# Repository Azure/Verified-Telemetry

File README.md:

# PROJECT ARCHIVED

This repository has been archived and is now read-only. It will continue to be available for viewing purposes, however caution should be used as security fixes are no longer being applied.

---

# Verified Telemetry for Azure IoT

## Overview

The quality of sensor data is fundamental for driving IoT adoption. Since IoT sensors are often made of low-cost components, deployed in-the-wild and in harsh environments, they are prone to failures leading to faulty or dirty data. The effect of this faulty data will lead to the well-known garbage-in / garbage-out process, leading to cascading ill-effects upstream and at times catastrophic decisions.  

Verified Telemetry (VT) is a state-of-the-art solution to determine the health of the sensor, i.e., working or faulty, which is consequently used to determine the quality of the sensed data. This is achieved by devising an intelligent “sensor fingerprint”, a set of unique electrical characteristics that differs between working and faulty sensors. The fingerprints can detect faults for a wide variety of off-the-shelf sensors and can be easily implemented with lightweight software code running on the IoT device. This novel approach empowers customers with a reliable and automated way to remotely measure and observe the health of the sensor in real-time alongside the data collected. The data associated with a validated fingerprint results in Verified Telemetry.

Verified Telemetry uses two technologies - FallCurve for analog sensors, CurrentSense for Digital Sensors. 

### Fall Curve

It reads the 

## API documentation

Refer to the [Verified Telemetry API](https://azure.github.io/Verified-Telemetry) for details on the VT Azure RTOS and FreeRTOS SDKs and how they are used.

## Resource Requirements

Verified Telemetry is designed to run on resource contrained MCUs, flash and RAM is limited. Below is our resource requirements for Verified Telemetry for a size optimized (-Os) binary:

| Type      | Size  |
| --------- | ----- |
| **Flash** | 13.0 kB |
| **RAM**   | 4.6 kB |

## Plug and Play

Verified Telemetry Library provides capabilities for interaction using a Plug and Play Model.
Details about this model can be found [here](./PnPModel).

## Samples

We provide multiple device and solution samples to showcase the usage of Verified Telemetry. Please follow the samples below to see Verified Telemetry in action.

To get you started with the device, refer to the following device samples for Azure RTOS and FreeRTOS:
* [Azure RTOS samples](https://github.com/Azure/Verified-Telemetry-Device-Sample)
* [FreeRTOS samples](https://github.com/Azure-Samples/Verified-Telemetry-FreeRTOS-Sample)

To get you started with the solution, refer to the following Grafana sample:
* [Grafana solution sample](https://github.com/Azure/Verified-Telemetry-Solution-Sample) showcases how Verified Telemetry can be utilized in real world scenarios.

## Using Verified Telemetry

Verified Telemetry utilizes CMake for building the project. To integrate Verified Telemetry into your projects build system follow these steps:

1. Using Git, submodule VT into your project:

    ```shell
    git submodule add https://github.com/Azure/Verified-Telemetry.git
    ```
1. In your CMake, set `VT_MIDDLEWARE_RTOS` to either `AZURE_RTOS` or `FREERTOS` depending on which middleware is appropriate for your project:

    ```cmake
    set(VT_MIDDLEWARE_RTOS "AZURE_RTOS")
    ```
1. In your CMake, add the VT directory:

    ```cmake
    add_subdirectory(verified-telemetry)
    ```
1. In your CMake, add VT into your targets link library:

    ```cmake
    target_link_libraries(${PROJECT_NAME}
        az::iot::vt
    )
    ```

## Porting to your Platform

Verified Telemetry requires platform specific functions to be defined at the application layer and then passed to VT during initialization.

> **NOTE**
> * Refer to [vt_device_driver.h](./inc/platform/vt_device_driver.h) for function declarations
> * Refer to [vt_device_driver_template.c](./templates/vt_device_driver_template.c) for a template for implementation of the platform functions.
> * Samples for implementation of platform functions can also be found in the [Device samples](https://github.com/Azure/Verified-Telemetry-Device-Sample/blob/main/MXChip/AZ3166/app/sample_vt_device_driver.c).

The application developer will implement the following functions:

 | Function  | Implementation Requirements  | FallCurve Required? |
 | --------- | ---------------------------- | ------------------- |
 | adc_single_init   | Initialize ADC when the controller and channel are passed as arguments         | REQUIRED |
 | adc_single_read   | Return ADC data when the controller and channel are passed as arguments        | REQUIRED |
 | adc_buffer_read   | Return buffer filled with ADC data using DMA/non-blocking read when the controller, channel, sampling frequency and sample length are passed as arguments | REQUIRED |
 | gpio_on           | Set a GPIO pin HIGH when the GPIO port and pin are passed as arguments         | REQUIRED |
 | gpio_off          | Set a GPIO pin LOW when the GPIO port and pin are passed as arguments          | REQUIRED |
 | tick_init         | Initialize a tick counter with a time resolution that is passed as an argument | REQUIRED |
 | tick_deinit       | De-initialize a running tick counter                                           | REQUIRED |
 | tick              | Return the present tick value                                                  | REQUIRED |
 | interrupt_enable  | Enable global interrupts on the MCU                                            | OPTIONAL |
 | interrupt_disable | Disable global interrupts on the MCU                                           | OPTIONAL |

## Support

If you need support, please see our [SUPPORT.md](./SUPPORT.md) file.

## Contributing

For details on contributing to this repository, see the [contributing](CONTRIBUTING.md) guide.

## Reporting Security Vulnerabilities

If you believe you have found a security vulnerability in any Microsoft-owned repository that meets Microsoft's definition of a security vulnerability, please report it to the [Microsoft Security Response Center](SECURITY.md).

## License

Verified Telemetry are licensed under the [MIT](LICENSE.txt) license.

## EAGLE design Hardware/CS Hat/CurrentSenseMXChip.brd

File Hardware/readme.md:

# PCB files for Verified Telemetry Hardware 

Includes Gerber, Assembly, Schematic, Board and BOM files for manufacturing of hardware required to setup Verified Telemetry on MX Chip, STM32 and ESP32. 
The hardware consists of CS hat and CS baseboards specific to MCU.

CS hat contains the components required to sample signals and communicate them to the MCU using SPI. CS hat gets fixed on the baseboard and no other wiring is required to setup the hardware. 

Baseboards are used to route the right pins on the MCU to the CS hat for VT functioning. 

## ST Microelectronics B-L475E-IOT01A / B-L4S5I-IOTOA1 Discovery kit Baseboard

## MXChip AZ3166 IoT DevKit Baseboard

## ESP 32 Baseboard

## CurrentSense (CS) Hat

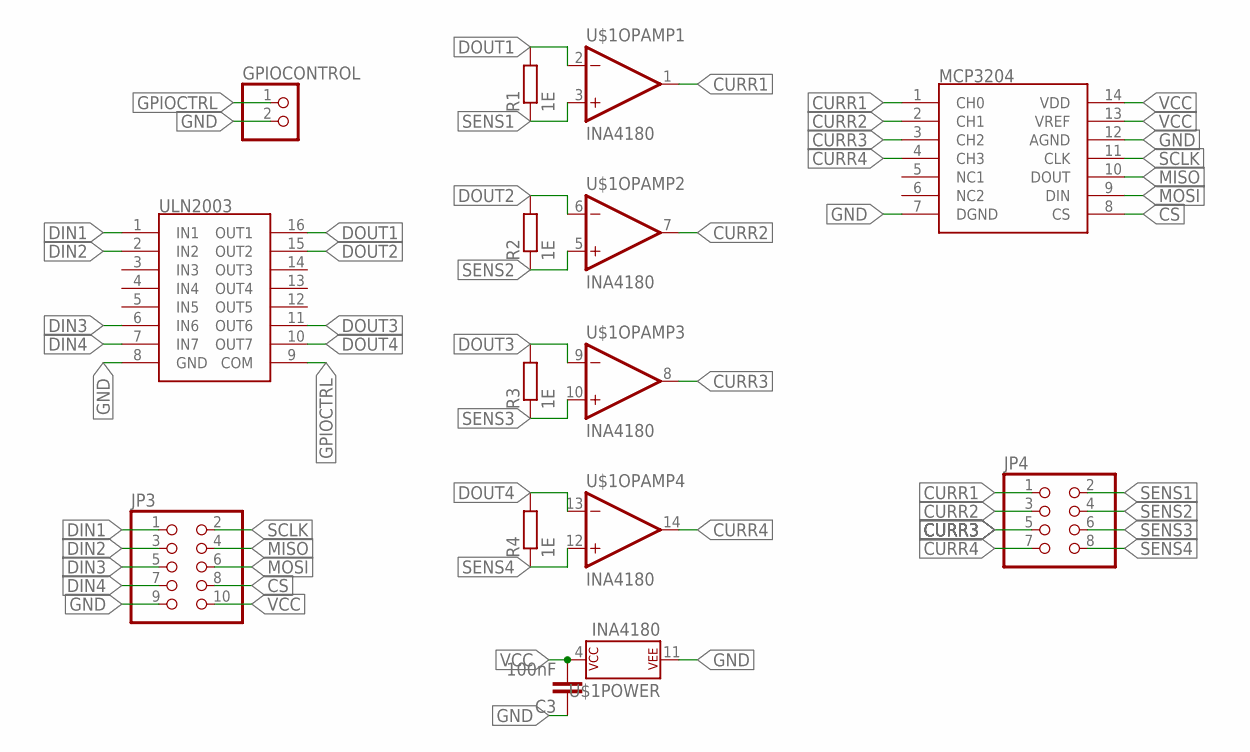
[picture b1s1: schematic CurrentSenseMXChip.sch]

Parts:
C3: 100nF; C1206
GPIOCONTROL: PINHD-1X2; 1X02
JP3: PINHD-2X5; 2X05
JP4: PINHD-2X4; 2X04
R1, R2, R3, R4: 1E; R1206
U$1: INA4180; TSSOP-14
U$2: ULN2003; SO16
U$3: MCP3204; TSSOP-14

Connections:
CS: JP3.8, U$3.8 (CS)
CURR1: JP4.1, U$1.1 (OUT), U$3.1 (CH0)
CURR2: JP4.3, U$1.7 (OUT), U$3.2 (CH1)
CURR3: JP4.5, U$1.8 (OUT), U$3.3 (CH2)
CURR4: JP4.7, U$1.14 (OUT), U$3.4 (CH3)
DIN1: JP3.1, U$2.1 (IN1)
DIN2: JP3.3, U$2.2 (IN2)
DIN3: JP3.5, U$2.6 (IN6)
DIN4: JP3.7, U$2.7 (IN7)
DOUT1: R1.2, U$1.2 (-IN), U$2.16 (OUT1)
DOUT2: R2.2, U$1.6 (-IN), U$2.15 (OUT2)
DOUT3: R3.2, U$1.9 (-IN), U$2.11 (OUT6)
DOUT4: R4.2, U$1.13 (-IN), U$2.10 (OUT7)
GND: C3.1, GPIOCONTROL.2, JP3.9, U$1.11 (P$V-), U$2.8 (GND), U$3.7 (DGND), U$3.12 (AGND)
GPIOCTRL: GPIOCONTROL.1, U$2.9 (COM)
MISO: JP3.4, U$3.10 (DOUT)
MOSI: JP3.6, U$3.9 (DIN)
SCLK: JP3.2, U$3.11 (CLK)
SENS1: JP4.2, R1.1, U$1.3 (+IN)
SENS2: JP4.4, R2.1, U$1.5 (+IN)
SENS3: JP4.6, R3.1, U$1.10 (+IN)
SENS4: JP4.8, R4.1, U$1.12 (+IN)
VCC: C3.2, JP3.10, U$1.4 (P$V+), U$3.13 (VREF), U$3.14 (VDD)

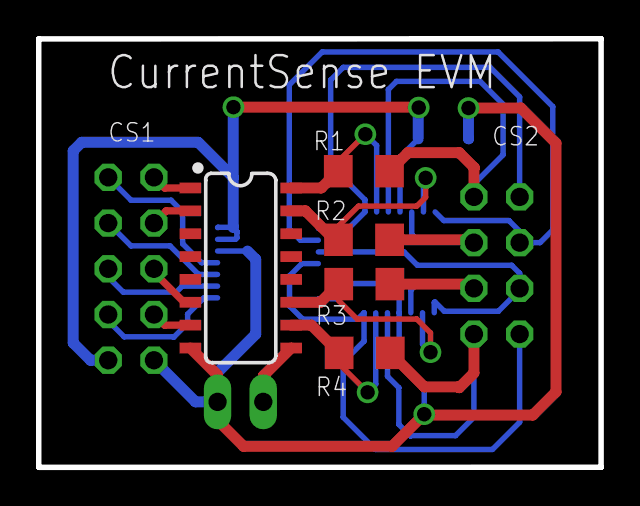
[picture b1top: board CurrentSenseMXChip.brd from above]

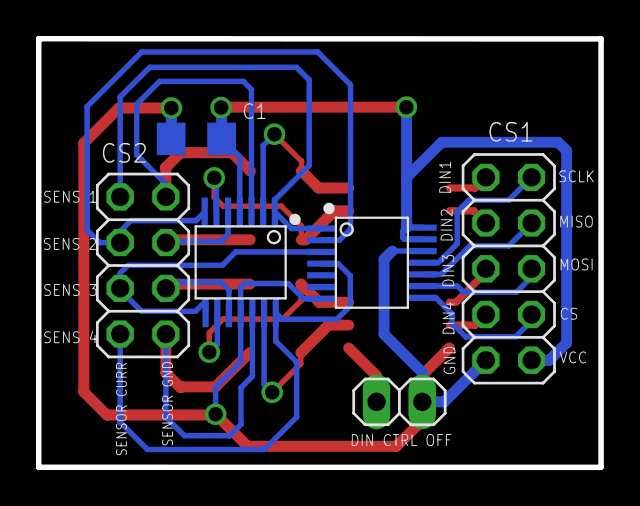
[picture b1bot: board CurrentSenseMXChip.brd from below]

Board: 2 copper layers, 31.2 x 23.8 mm, 11 parts (6 on the bottom side), 23 nets.

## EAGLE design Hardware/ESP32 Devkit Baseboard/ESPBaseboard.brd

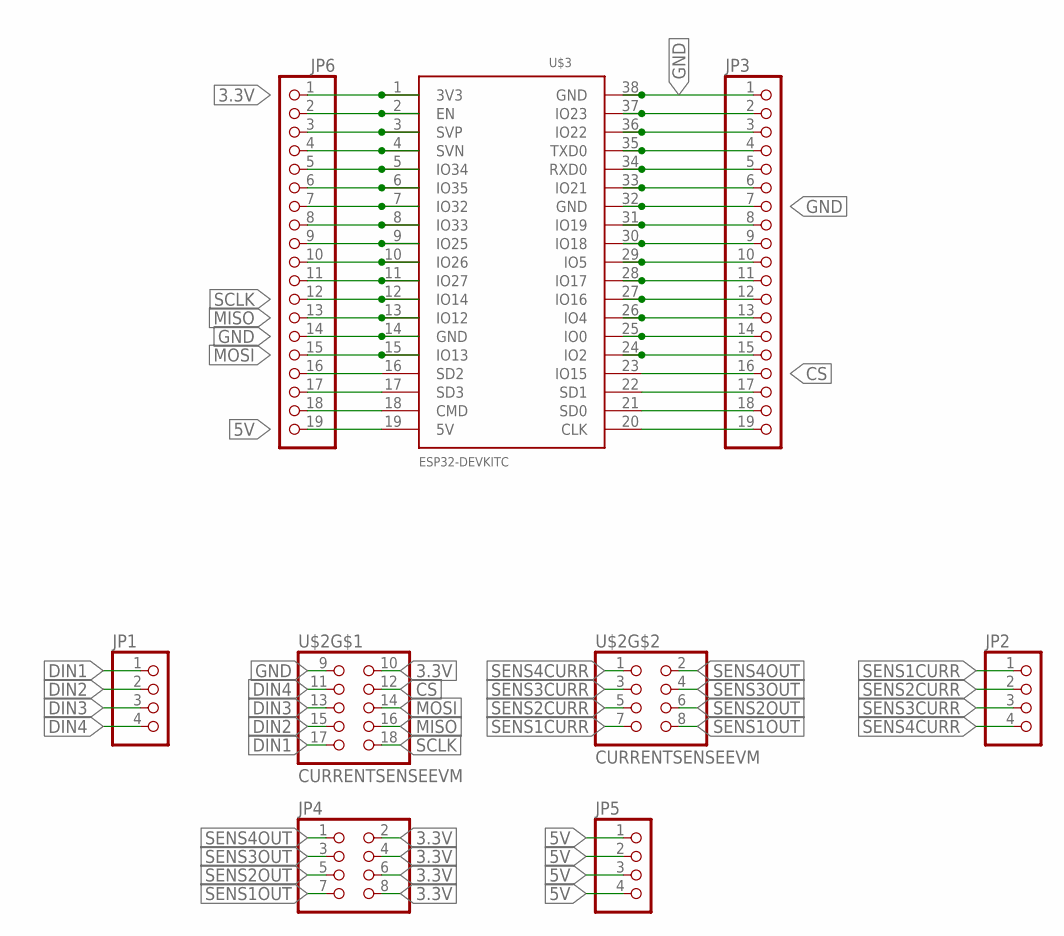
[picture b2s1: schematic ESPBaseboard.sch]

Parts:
JP1, JP2, JP5: PINHD-1X4; 1X04
JP3, JP6: PINHD-1X19; 1X19
JP4: PINHD-2X4; 2X04
U$2: CURRENTSENSEEVM
U$3: ESP32DEVKITC; ESP32-DEVKITC

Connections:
3.3V: JP4.2, JP4.4, JP4.6, JP4.8, JP6.1, U$2.10 (2), U$3.1 (3V3)
5V: JP5.1, JP5.2, JP5.3, JP5.4, JP6.19, U$3.19 (5V)
CS: JP3.10, JP3.16, U$2.12 (4), U$3.23 (IO15), U$3.29 (IO5)
DIN1: JP1.1, U$2.17 (9)
DIN2: JP1.2, U$2.15 (7)
DIN3: JP1.3, U$2.13 (5)
DIN4: JP1.4, U$2.11 (3)
GND: JP3.1, JP3.7, JP6.14, U$2.9 (1), U$3.14 (GND), U$3.32 (GND), U$3.38 (GND)
MISO: JP3.8, JP6.13, U$2.16 (8), U$3.13 (IO12), U$3.31 (IO19)
MOSI: JP3.2, JP6.15, U$2.14 (6), U$3.15 (IO13), U$3.37 (IO23)
unnamed: JP6.2, U$3.2 (EN)
unnamed: JP6.3, U$3.3 (SVP)
unnamed: JP6.4, U$3.4 (SVN)
unnamed: JP6.5, U$3.5 (IO34)
unnamed: JP6.7, U$3.7 (IO32)
unnamed: JP6.8, U$3.8 (IO33)
unnamed: JP6.9, U$3.9 (IO25)
unnamed: JP6.10, U$3.10 (IO26)
unnamed: JP6.11, U$3.11 (IO27)
unnamed: JP3.3, U$3.36 (IO22)
unnamed: JP3.4, U$3.35 (TXD0)
unnamed: JP3.5, U$3.34 (RXD0)
unnamed: JP3.6, U$3.33 (IO21)
unnamed: JP3.11, U$3.28 (IO17)
unnamed: JP3.12, U$3.27 (IO16)
unnamed: JP3.13, U$3.26 (IO4)
unnamed: JP3.14, U$3.25 (IO0)
unnamed: JP3.15, U$3.24 (IO2)
unnamed: JP6.16, U$3.16 (SD2)
unnamed: JP6.17, U$3.17 (SD3)
unnamed: JP6.18, U$3.18 (CMD)
unnamed: JP3.19, U$3.20 (CLK)
unnamed: JP3.18, U$3.21 (SD0)
unnamed: JP3.17, U$3.22 (SD1)
SCLK: JP3.9, JP6.6, JP6.12, U$2.18 (10), U$3.6 (IO35), U$3.12 (IO14), U$3.30 (IO18)
SENS1CURR: JP2.1, U$2.7
SENS1OUT: JP4.7, U$2.8
SENS2CURR: JP2.2, U$2.5
SENS2OUT: JP4.5, U$2.6
SENS3CURR: JP2.3, U$2.3
SENS3OUT: JP4.3, U$2.4
SENS4CURR: JP2.4, U$2.1
SENS4OUT: JP4.1, U$2.2

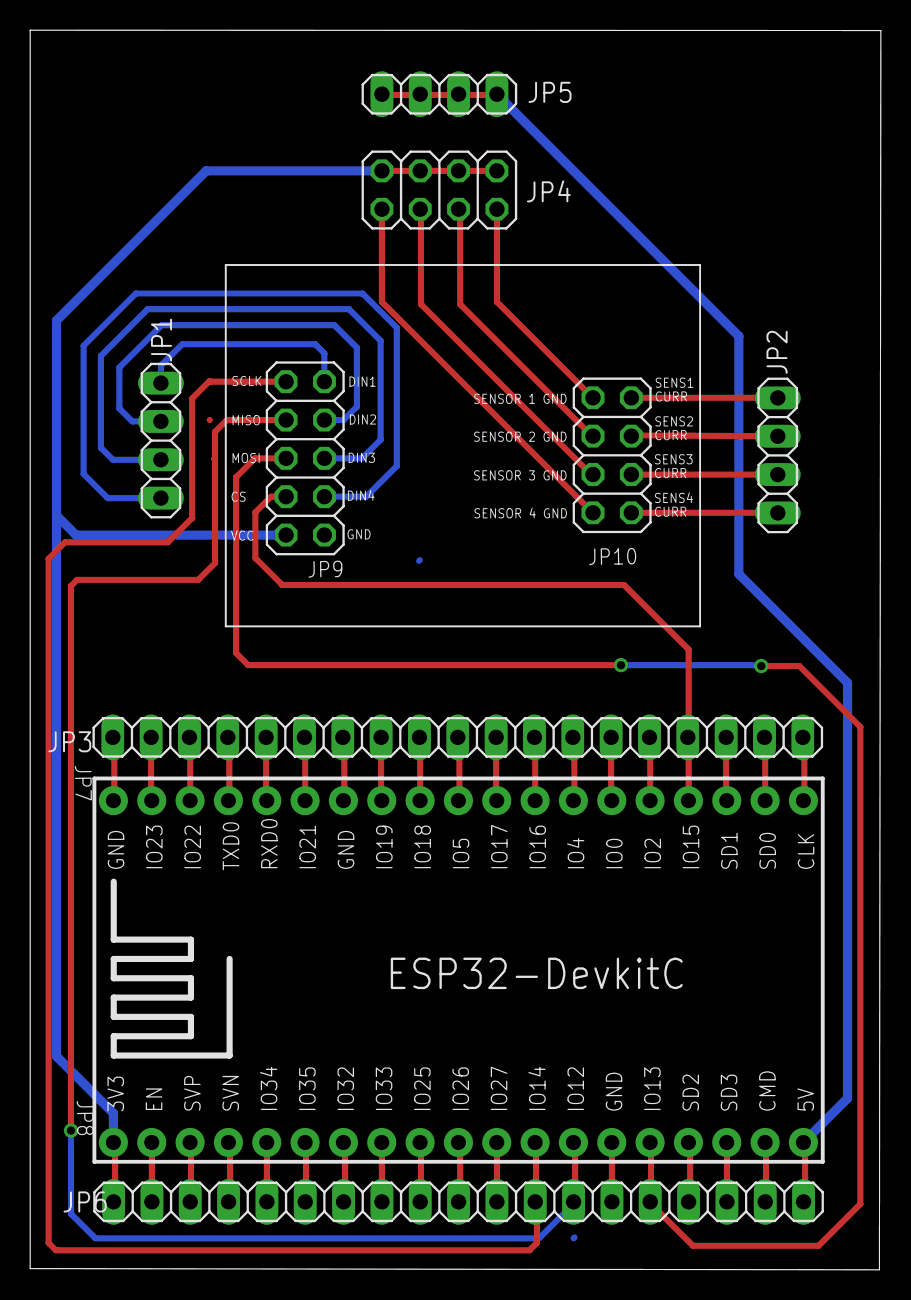
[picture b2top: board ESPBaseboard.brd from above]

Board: 2 copper layers, 56.4 x 82.1 mm, 8 parts (0 on the bottom side), 43 nets.

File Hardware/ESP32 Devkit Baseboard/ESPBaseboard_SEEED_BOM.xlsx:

Designator | Manufacturer Part Number | Qty | Link
JP1,JP2,JP5 | SSW-104-02-T-S | 3 | SSW-104-02-T-S Samtec Inc. | Connectors, Interconnects | DigiKey
JP3,JP6,JP7,JP8 | SSW-119-02-T-S | 4 | SSW-119-02-T-S Samtec Inc. | Connectors, Interconnects | DigiKey
JP4,JP10 | PPTC042LFBN-RC | 2 | PPTC042LFBN-RC Sullins Connector Solutions | Connectors, Interconnects | DigiKey
JP9 | PPTC052LFBN-RC | 1 | PPTC052LFBN-RC Sullins Connector Solutions | Connectors, Interconnects | DigiKey

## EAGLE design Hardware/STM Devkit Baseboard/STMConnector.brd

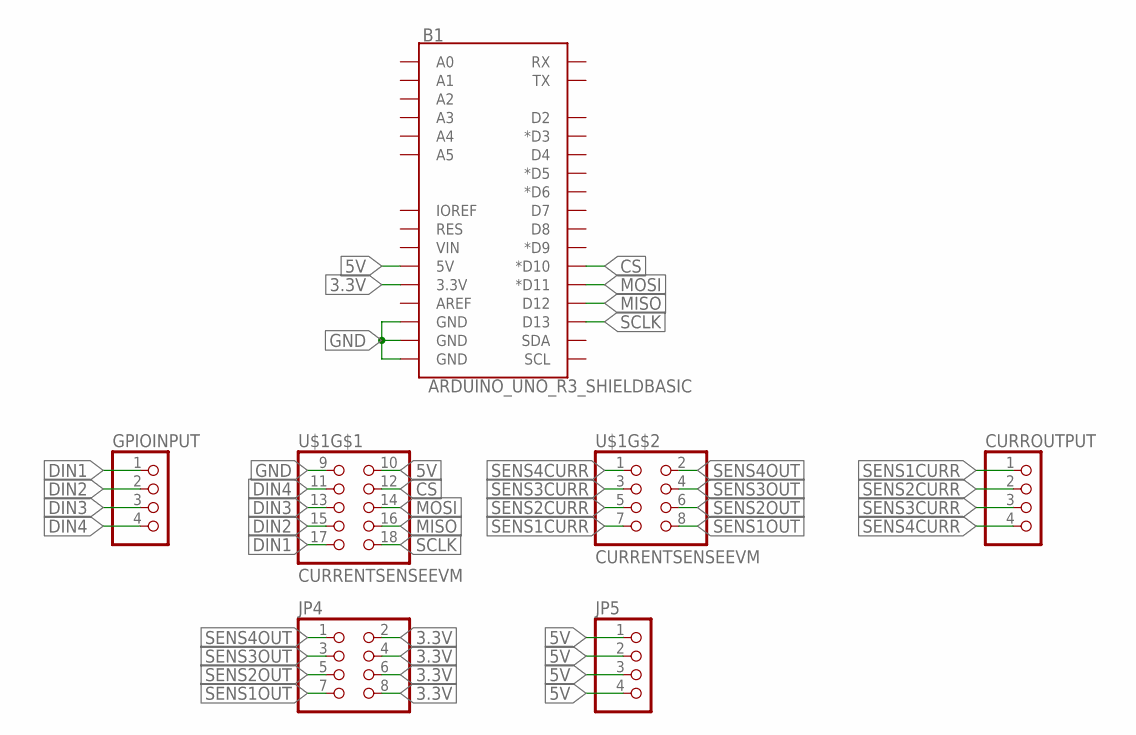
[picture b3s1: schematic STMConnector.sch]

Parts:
B1: ARDUINO_UNO_R3_SHIELDBASIC; UNO_R3_SHIELD
CURROUTPUT: PINHD-1X4; 1X04
GPIOINPUT: PINHD-1X4; 1X04
JP4: PINHD-2X4; 2X04
JP5: PINHD-1X4; 1X04
U$1: CURRENTSENSEEVM

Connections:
3.3V: B1.3.3V, JP4.2, JP4.4, JP4.6, JP4.8
5V: B1.5V, JP5.1, JP5.2, JP5.3, JP5.4, U$1.10 (2)
CS: B1.D10 (*D10), U$1.12 (4)
DIN1: GPIOINPUT.1, U$1.17 (9)
DIN2: GPIOINPUT.2, U$1.15 (7)
DIN3: GPIOINPUT.3, U$1.13 (5)
DIN4: GPIOINPUT.4, U$1.11 (3)
GND: B1.GND@0 (GND), B1.GND@1 (GND), B1.GND@2 (GND), U$1.9 (1)
MISO: B1.D12, U$1.16 (8)
MOSI: B1.D11 (*D11), U$1.14 (6)
SCLK: B1.D13, U$1.18 (10)
SENS1CURR: CURROUTPUT.1, U$1.7
SENS1OUT: JP4.7, U$1.8
SENS2CURR: CURROUTPUT.2, U$1.5
SENS2OUT: JP4.5, U$1.6
SENS3CURR: CURROUTPUT.3, U$1.3
SENS3OUT: JP4.3, U$1.4
SENS4CURR: CURROUTPUT.4, U$1.1
SENS4OUT: JP4.1, U$1.2

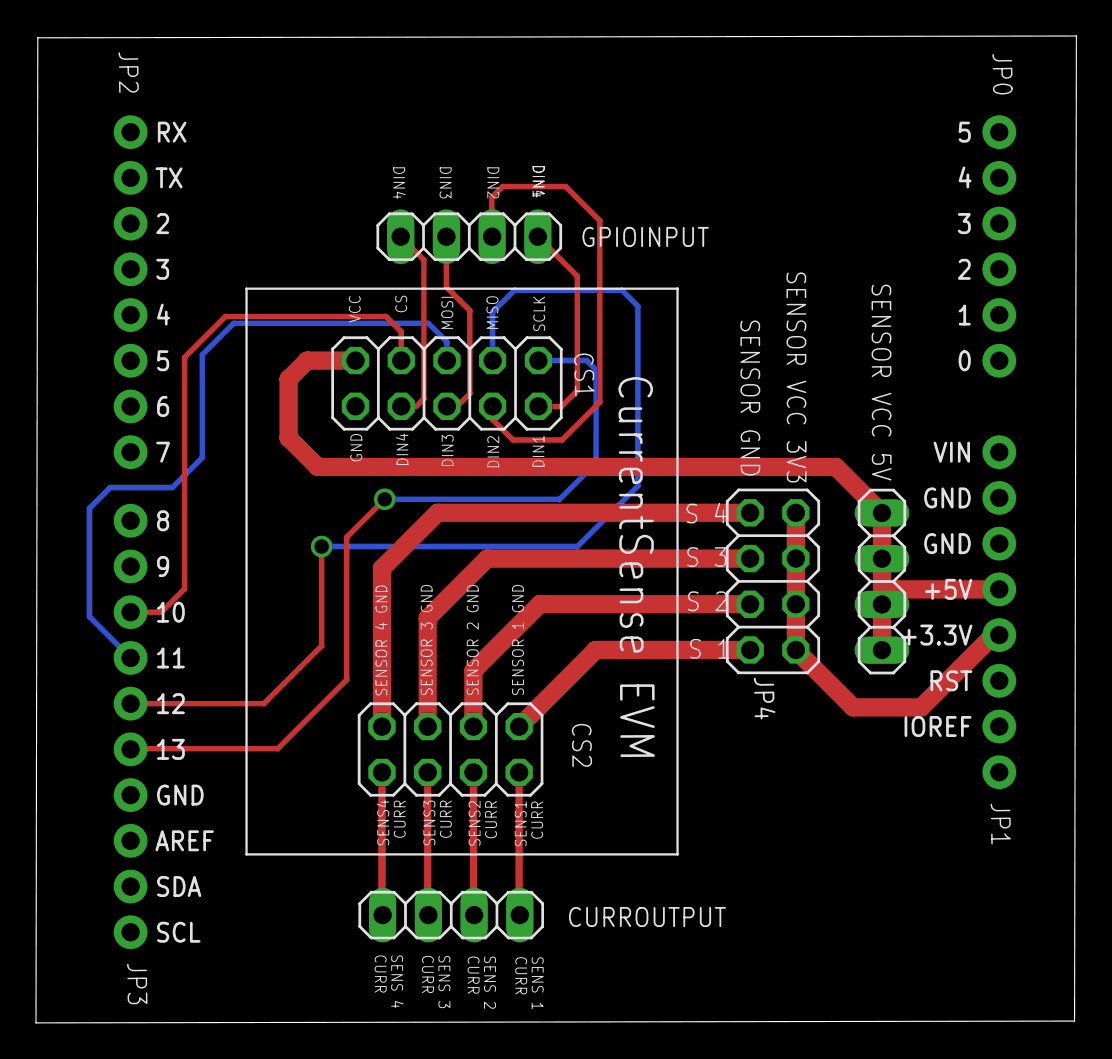
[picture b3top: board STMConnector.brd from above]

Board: 2 copper layers, 57.8 x 54.8 mm, 6 parts (0 on the bottom side), 19 nets.

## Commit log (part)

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2021-01-29 Added License.txt file (MIT License)
2021-01-29 add open source artifacts
2021-01-30 Replaced uint with uint32_t in core,platform
2021-01-30 _vt_database_initialize_fingerpintdb spelling corrected
2021-02-01 Removed standard libraries from vt_api.h
2021-02-01 Declared internally used functions as static
2021-02-01 Applied Clang
2021-02-01 Changed double to float
2021-02-01 Moved reported property parsing to helper function
2021-02-09 Add retrain fingerprint command
2021-02-13 Chnages to Readme
2021-02-13 Changes to readme
2021-02-15 Shifted Calibration to ResetFingerprint Command
2021-02-15 Updated Calibration parameters for us delay
2021-02-17 Updated Serial Debug Comments
2021-02-17 Sync+Debug fixes
2021-02-17 Improve debug statements
2021-02-18 Updated Calibration serial debug statements
2021-02-18 Updated Calibration printing if-else conditions
2021-02-18 Update Print Statements
2021-02-19 Fix retrain command potential bug
2021-02-19 Fix fallTime sync issue
2021-03-01 Incorrect falltime bugfix
2021-03-02 fix template collection and sync
2021-03-02 evaluation fixes
2021-03-04 Added Debug print MACRO
2021-03-05 send desired properties at boot
2021-03-05 fix send desired properties at boot
2021-03-05 changed debug macros
2021-03-09 Increased Sampling time for ADC conversion
2021-03-09 Updated Frequency range for calibration
2021-03-10 update PnP Model for 2 SM
2021-03-22 Added tests folder
2021-03-22 Added template functions for unit tests
2021-03-22 Added unit test callback functions for vt_fingerprint
2021-03-22 Added Implementations for max and min index unit tests
2021-03-26 Added CMakes for core and platform modules
    (Check C2057 Error)
2021-03-26 Added #undef for Custom Device
2021-03-26 Resolved C4244 Warnings
2021-03-26 Removed redundant test cases
2021-03-29 Removed vt::core dependency from vt::platform
    Error codes to be reviewed
2021-03-30 Changed CMake Structure
2021-03-31 Added Test cases for calculate shape and 37index
2021-03-31 Added Unit tests for Fingerprint Evaluate functions
2021-03-31 Added Epsilon to remove rounding off issue
2021-03-31 Added Test Cases for Calculate Pearson Coefficient and Fall Time
2021-03-31 Unit testing (#5)
    * Added Test cases for calculate shape and 37index
    * Added Unit tests for Fingerprint Evaluate functions
    * Added Epsilon to remove rounding off issue
    * Added Correlation coefficient test case
    * Added Test Cases for Calculate Pearson Coefficient and Fall Time
2021-04-01 Added unit testing Template functions for database module
2021-04-01 Added unit tests for database initialize functions
2021-04-01 Added Unit tests for falltime and pearson coefficient store functions
2021-04-02 Added Setup and Teardown functions for database unit tests
2021-04-02 Added Unit tests for database evaluate module
2021-04-02 Added Unit tests for database fetch module
2021-04-02 Turned OFF unit testing by default
2021-04-02 Removed vt_dsc.h from vt_api.h and added it specific c source files.
2021-04-05 Updated Datatypes
2021-04-05 Updated from camel case to small case
2021-04-05 Removed unused libraries from vt_database.h
2021-04-05 Removed enum comments
2021-04-05 Updated vt_database_evaluate.c
2021-04-05 Updated storeinflash to _vt_database_store_flash
2021-04-05 Defined _vt_fingerprint_calculate_minimum_index as static
2021-04-05 Grouped Static functions at the top of source files
2021-04-05 Updated _vt_fingerprint_evaluate_correlation_coefficient
2021-04-05 add message properties
2021-04-05 Updated magic numbers with #defines
2021-04-05 add github actions
2021-04-05 update link check to main branch
2021-04-05 update cmocka fetching
2021-04-05 fix unit testing flag
2021-04-05 add missing cmocka includes
2021-04-05 add missing include
2021-04-05 only add libm for non-win32
2021-04-05 verbose output for unit test
2021-04-06 Shifted vt_debug.h from vt_api.h to specific source files
2021-04-06 Added VT_FLASH_FINGERPRINT_LENGTH macro
2021-04-06 Shifted Macro to vt_api.h
2021-04-06 Changed Directory structure
    Added internal directory
2021-04-06 Removed Database Storage in Flash
2021-04-06 Removed Flash from readme
2021-04-06 Updated Data Types
2021-04-07 Added "app_common" library in CMake for vt_middleware
2021-04-07 Updated Datatypes in unit tests
2021-04-07 Removed app_common from stanalone build link library list
2021-04-07 Applied Clang to all files
2021-04-07 Added templates for sensor module unit tests
2021-04-07 Test commit
2021-04-08 Added Parameter Checking in ADC Read
2021-04-08 Added Unit tests for vt_sensor_initialize()
2021-04-08 Removed vt_database_clear function
2021-04-09 Added wrap functions for vt_platform
2021-04-09 Added unit test for vt_sensor_fingerprint_read()
2021-04-09 Resolved failed vt_sensor test cases
2021-04-09 Removed function call check for vt_dsc_delay
2021-04-09 Removed Parameter check for vt_dsc_delay
2021-04-11 test
2021-04-12 Unit testing (#15)
    * Added templates for sensor module unit tests
    * Added Wrap function for ADC read
    * Update test_vt_sensor.c
    * Added Parameter Checking in ADC Read
    * Added Unit tests for vt_sensor_initialize()
    * Added wrap functions for vt_platform
2021-04-12 Resolved Calibration build errors
2021-04-12 Added Fingerprints to Calibration Unit test
2021-04-12 Added exponential_fall in vt_sensor_fingerprint_read
2021-04-12 cleanup
2021-04-12 fix variable
2021-04-12 add test coverage
2021-04-12 Moved fingerprint array and string to stack memory
2021-04-12 Testing Calibration
2021-04-13 update to gcovr
2021-04-13 Added unit test for vt_sensor_read_status()
2021-04-13 Added Comments
2021-04-13 Unit testing (#16)
    * Added templates for sensor module unit tests
    * Added Wrap function for ADC read
    * Update test_vt_sensor.c
    * Added Parameter Checking in ADC Read
    * Added Unit tests for vt_sensor_initialize()
    * Added wrap functions for vt_platform
2021-04-14 refine codecov upload
2021-04-14 Exclude custom driver
2021-04-14 initial code coverage (#17)
    * initial code coverage
    * cleanup
    * fix variable
    * add test coverage
    * remove script
    * update to gcovr
2021-04-14 add code coverage
2021-04-15 Added vt_debug in vt:platform
2021-04-15 Updated naming convention
2021-04-19 Added corner cases for database evaluate
2021-04-19 Added corner test cases for database fetch
2021-04-19 Added Corner test cases for sensor read
2021-04-19 add CTest
2021-04-19 include CTest
2021-04-20 Added noise curve test case for calibration unit testing
2021-04-20 Added Additional curve for calibration testing
2021-04-22 Removed strdup to resolve memory leak
2021-04-22 Updated strcpy with strncpy for avoid buffer overflow
2021-04-23 Added fingerprint_string_length check to avoid buffer overflow
2021-05-03 long int fix
2021-05-03 test fixes
2021-05-03 fix misclassification
2021-05-03 update timer init deinit
2021-05-05 modify calibration evaluation
2021-05-07 core updated
2021-05-10 update cmake
2021-05-10 bug-fixes
2021-05-11 currentsense first push
2021-05-17 comment_fixes
2021-05-17 clang format
2021-05-18 fixed doxygen for extern wrapper
2021-05-18 add doxygen
2021-05-18 add docs github pages deploy workflow
2021-05-18 initial doxygen github page integration
2021-05-18 deploy: 056c448a0093b17964d18cd18aac5222f42c092f
2021-05-18 fix workflow job name
2021-05-18 deploy: d5a2306831927f1ded1ec6402f3463beebaff762
2021-05-18 remove buld from PR for docs
2021-05-18 initial doxygen github page integration (#27)
    * initial doxygen github page integration
    * fix workflow job name
    * update html location
    * remove buld from PR for docs
2021-05-18 build workflow on public_preview_1 branch
2021-05-18 clang format (#26)
    * clang format
    * more clang format updates
    * fixed doxygen for extern wrapper
    * add doxygen
    * add docs github pages deploy workflow
    * update doxygen
2021-05-18 fix pages publish dir
2021-05-18 deploy: e3df0d5a1aa4ffe775228ab76ebde00116d24ccc
2021-05-18 fix job name for doxygen build
2021-05-18 update main readme to point at doxygen API docs
2021-05-18 Ryanwinter/api docs (#28)
    * convert docs from VT_API.md to doxygen
    * update main readme to point at doxygen API docs
2021-05-18 deploy: 31f54de85cc5b0b59897ca50cc54fdac95ce5e55
2021-05-18 remove @file file_name as its derived automatically.
2021-05-20 reformat workflow trigger
2021-05-21 review_fixes_1
2021-05-23 deploy: a0558ebf0c1310a605df39a2acbf1a4c00697241
2021-05-24 add notice.txt with no external dependencies
2021-05-24 test cases update (#34)
2021-05-24 Public preview 1 (#29)
    * clang format
    * add doxygen
    * add docs github pages deploy workflow
    * format on save for clang
    generate doxygen on preview branch
    * build workflow on public_preview_1 branch
2021-05-25 fix bug in vt_fc_read.c
2021-05-25 Add doxygen comments
2021-05-26 Documentation update (#36)
    * Update README.md
    * Add doxygen comments
    * Update README.md
    * Update README.md
2021-05-26 Update build-docs.yaml (#37)
2021-06-03 add new test cases
2021-06-03 fix tests
2021-06-03 fix more tests
2021-06-08 add new test cases (#39)
    * add new test cases
    * fix tests
    * Update test_vt_fc_object_sensor.c
    * fix more tests
    * Update test_vt_fc_object_sensor.c
    * add test for pearson coeff
2021-06-08 deploy: 0e1d294c2fdb9f76d689f7087580d3f57095b0b4
2021-06-11 convert magic number to macro
2021-06-18 first push
2021-06-18 bugfixes
2021-06-23 bug fixes
2021-06-24 Update README.md
    point to device driver header and template in readme
2021-06-25 bugfix for device status not updating
2021-07-13 logic fixes
2021-07-13 add tests for vt_currentsense_object_signature_process()
2021-07-14 logic fixes
    Conversion of current draw to binary waveform had issues when seedpoints had same value
2021-07-14 logic fixes
    Remove CS Init seg fault, make database fetch robust
2021-07-14 add tests
2021-07-15 Feature/currentsense update v2 (#41)
    * first push
    * Update CMakeLists.txt
    * bugfixes
    * review fixes
    * bug fixes
    * review fixes
2021-07-20 vt middleware for freertos
2021-07-20 fix cmake
2021-07-20 add test for vt_currentsense_object_signature_read()
2021-07-20 Feature/test cases (#42)
    * format file
    * add test for vt_currentsense_object_signature_read()
2021-07-23 structure changes
2021-07-26 workflow
2021-07-26 new test cases
2021-07-26 test cases
2021-08-06 update logging of fingerprint after DC
2021-08-09 fixed delay in sensor status
2021-08-09 test cases & fix delay in sensor status (#47)
    * fixed delay in sensor status
    * test cases update
2021-08-14 Doxygen update (#48)
2021-08-14 deploy: 6c3fe8bf553d6a307edc43d7ca84864f00b05662
2021-08-26 vt_fc_read fix & reset fingerprint crash fix
2021-09-10 middleware update
2021-09-23 formatting update
2021-09-29 Common VT library (#49)
    * formatting update
    * test cases
    * Doxygen comments
2021-10-06 Break up CMake across multiple files, update readme and doxygen
2021-10-06 formating fix
2021-10-06 rework resource requirements
2021-10-07 various changes based on comments.
2021-10-07 define update
2021-10-08 remove unused header, use strtok instead of strtok_r for compatibility
2021-10-08 Additional of FreeRTOS SDK (#51)
    * vt middleware for freertos
    * fix cmake
    * cleanup
    * structure changes
    * first push
    * log update
2021-10-08 deploy: 01aa78f3e1fbe7b36e19cc9b7d07eaccc60db0d1
2021-10-08 deploy: a0ec5bd233ef58425866578053337f2b7c343c3e
2021-10-08 fix API markdown numbering
2021-10-08 add freertos includes
2021-10-12 CurrentSense Update
2021-10-12 update flash and RAM usage for debug build.
2021-11-01 command always return success
2021-11-30 CS + freertos update
2022-02-23 Updated ACR
2022-03-17 warning fixes
2022-03-21 Average status and multicalib count update
2022-03-25 Master version
2022-04-18 Rep, non rep OR
2022-04-18 Peaks less than 3 update
2022-04-22 Rename readme file
2022-04-25 debug update
2022-04-26 cmake update
2022-04-26 switch to profiling target to enable gcov
2022-04-26 change build path
2022-04-26 enable verbose cmake build
2022-04-29 new device fix
2022-04-29 test case update
2022-04-29 Features/currentsense (#54)
    * CurrentSense Update
    * CS + freertos update
    * Updated ACR
    * VT STM Multisampling update
    * warning fixes
    * Average status and multicalib count update
2022-05-06 VT Status Update
2022-05-06 VT Status Update (#55)
2022-05-09 New Testcases
2022-08-29 CS v2.0
2022-09-05 Update test cases
2023-05-24 CurrentSense Improvements

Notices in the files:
parts and their libraries:
SparkFun-IC-Amplifiers: Licensing: Creative Commons ShareAlike 4.0 International - https://creativecommons.org/licenses/by-sa/4.0
